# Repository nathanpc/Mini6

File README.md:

# Mini6

A mini 3 watts per channel amplifier.

## Schematic

It's a very simple amplifier with a op-amp based pre-amp and buffered volume control followed by a small power amplifier with a [CFP output stage](http://en.wikipedia.org/wiki/Sziklai_pair).

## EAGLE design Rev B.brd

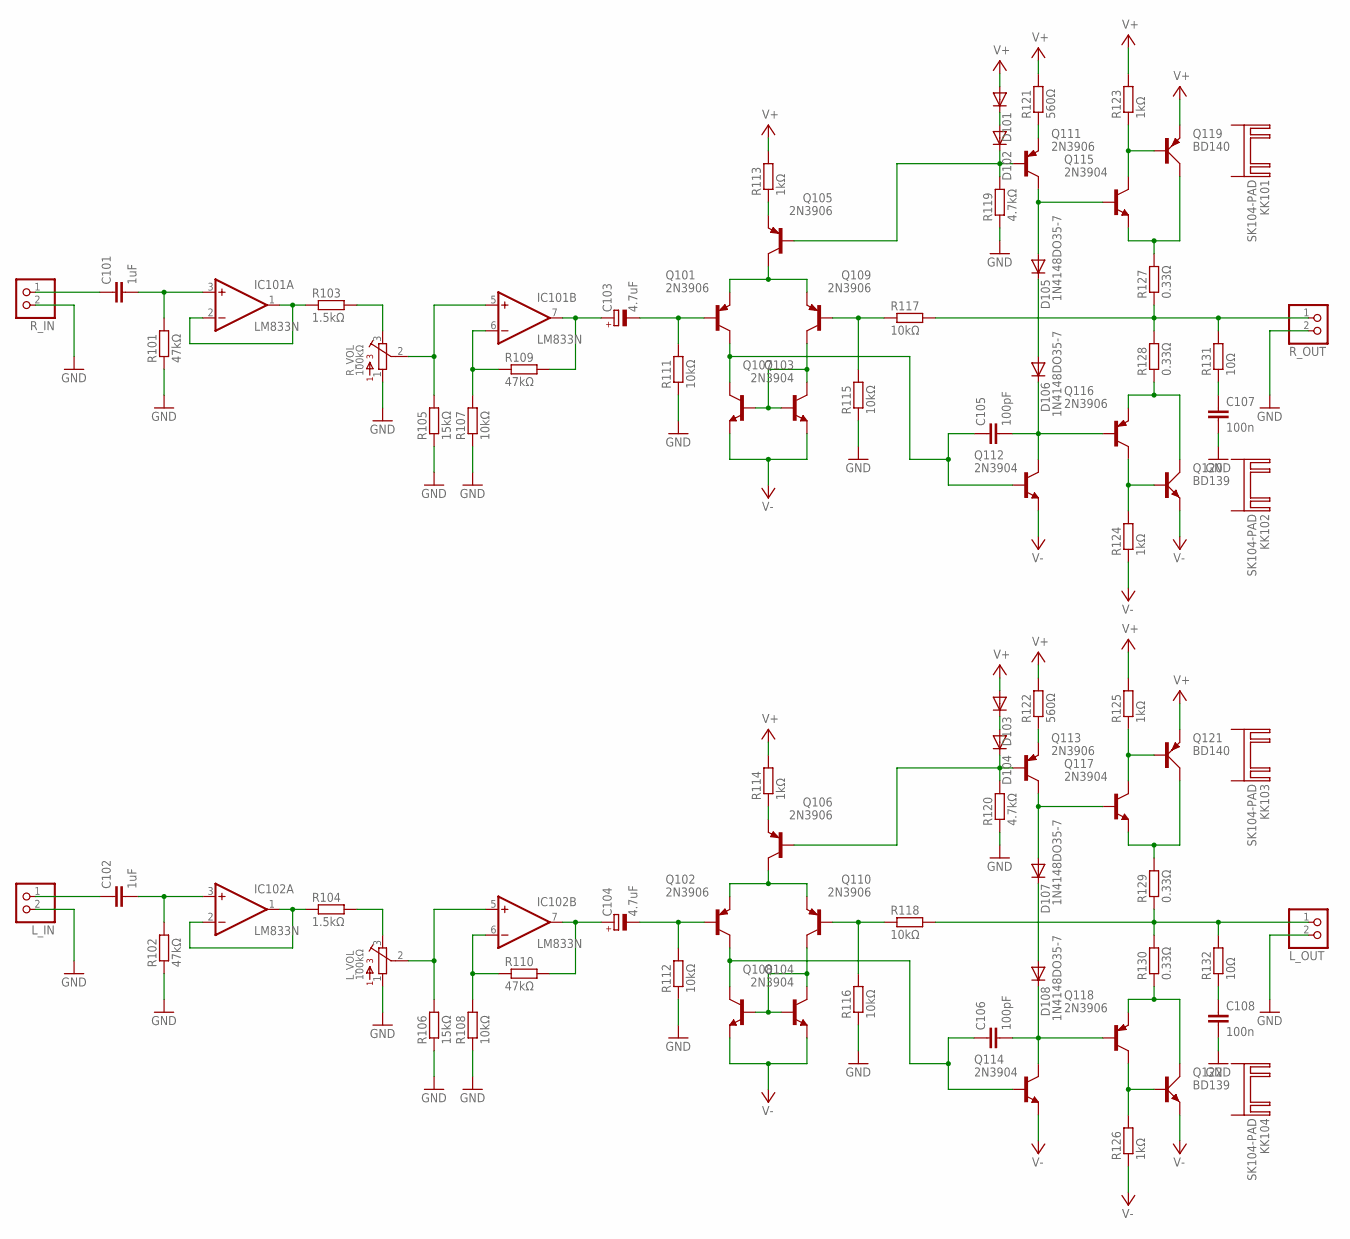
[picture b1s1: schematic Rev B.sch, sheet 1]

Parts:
C101, C102: 1uF; C150-072X183
C103, C104: 4.7uF; E2-5
C105, C106: 100pF; C050-050X075
C107, C108: 100n; C075-042X103
D101, D102, D103, D104, D105, D106, D107, D108: 1N4148DO35-7; DO35-7
IC101, IC102: LM833N; DIL08
KK101, KK102, KK103, KK104: SK104-PAD
L_IN: JST_2PIN-THM; JST-PH-2-THM
L_OUT: JST_2PIN-THM; JST-PH-2-THM
L_VOL: 100kΩ; 3362U
Q101, Q102, Q105, Q106, Q109, Q110, Q111, Q113, Q116, Q118: 2N3906; TO92
Q103, Q104, Q107, Q108, Q112, Q114, Q115, Q117: 2N3904; TO92
Q119, Q121: BD140; TO126AV
Q120, Q122: BD139; TO126AV
R101, R102, R109, R110: 47kΩ; 0207/10
R103, R104: 1.5kΩ; 0207/10
R105, R106: 15kΩ; 0207/10
R107, R108, R111, R112, R115, R116, R117, R118: 10kΩ; 0207/10
R113, R114, R123, R124, R125, R126: 1kΩ; 0207/10
R119, R120: 4.7kΩ; 0207/10
R121, R122: 560Ω; 0207/10
R127, R128, R129, R130: 0.33Ω; 0309/12
R131, R132: 10Ω; 0617V
R_IN: JST_2PIN-THM; JST-PH-2-THM
R_OUT: JST_2PIN-THM; JST-PH-2-THM
R_VOL: 100kΩ; 3362U

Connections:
GND: C107.2, C108.2, L_IN.2 (1), L_OUT.2 (1), L_VOL.1, R101.1, R102.1, R105.1, R106.1, R107.1, R108.1, R111.1, R112.1, R115.1, R116.1, R119.1, R120.1, R_IN.2 (1), R_OUT.2 (1), R_VOL.1; also elsewhere on the board
L_OUT: L_OUT.1 (2), R118.2, R129.1, R130.2, R132.2
unnamed: D105.A, Q111.1 (C), Q115.2 (B)
unnamed: Q101.3 (E), Q105.1 (C), Q109.3 (E)
unnamed: Q103.2 (B), Q107.1 (C), Q107.2 (B), Q109.1 (C)
unnamed: Q104.2 (B), Q108.1 (C), Q108.2 (B), Q110.1 (C)
unnamed: C103.-, Q101.2 (B), R111.2
unnamed: C103.+, IC101.7 (OUT), R109.2
unnamed: C101.1, R_IN.1 (2)
unnamed: C105.1, Q101.1 (C), Q103.1 (C), Q112.2 (B)
unnamed: C101.2, IC101.3 (+IN), R101.2
unnamed: IC102.1 (OUT), IC102.2 (-IN), R104.1
unnamed: IC102.5 (+IN), L_VOL.2, R106.2
unnamed: L_VOL.3, R104.2
unnamed: IC102.6 (-IN), R108.2, R110.1
unnamed: C102.1, L_IN.1 (2)
unnamed: C102.2, IC102.3 (+IN), R102.2
unnamed: Q105.3 (E), R113.1
unnamed: Q111.3 (E), R121.1
unnamed: D102.C, Q105.2 (B), Q111.2 (B), R119.2
unnamed: D101.C, D102.A
unnamed: C107.1, R131.1
unnamed: C108.1, R132.1
unnamed: Q106.3 (E), R114.1
unnamed: D105.C, D106.A
unnamed: C104.-, Q102.2 (B), R112.2
unnamed: Q115.1 (C), Q119.B, R123.1
unnamed: Q116.1 (C), Q120.B, R124.2
unnamed: Q116.3 (E), Q120.C, R128.1
unnamed: Q115.3 (E), Q119.C, R127.2
unnamed: C104.+, IC102.7 (OUT), R110.2
unnamed: C105.2, D106.C, Q112.1 (C), Q116.2 (B)
unnamed: Q109.2 (B), R115.2, R117.1
unnamed: Q102.3 (E), Q106.1 (C), Q110.3 (E)
unnamed: C106.1, Q102.1 (C), Q104.1 (C), Q114.2 (B)
unnamed: D107.C, D108.A
unnamed: D107.A, Q113.1 (C), Q117.2 (B)
unnamed: Q117.1 (C), Q121.B, R125.1
unnamed: Q117.3 (E), Q121.C, R129.2
unnamed: Q118.1 (C), Q122.B, R126.2
unnamed: Q118.3 (E), Q122.C, R130.1
unnamed: C106.2, D108.C, Q114.1 (C), Q118.2 (B)
unnamed: Q110.2 (B), R116.2, R118.1
unnamed: Q113.3 (E), R122.1
unnamed: D104.C, Q106.2 (B), Q113.2 (B), R120.2
unnamed: D103.C, D104.A
unnamed: IC101.1 (OUT), IC101.2 (-IN), R103.1
unnamed: IC101.5 (+IN), R105.2, R_VOL.2
unnamed: R103.2, R_VOL.3
unnamed: IC101.6 (-IN), R107.2, R109.1
R_OUT: R117.2, R127.1, R128.2, R131.2, R_OUT.1 (2)
V+: D101.A, D103.A, Q119.E, Q121.E, R113.2, R114.2, R121.2, R122.2, R123.2, R125.2; also elsewhere on the board
V-: Q103.3 (E), Q104.3 (E), Q107.3 (E), Q108.3 (E), Q112.3 (E), Q114.3 (E), Q120.E, Q122.E, R124.1, R126.1; also elsewhere on the board

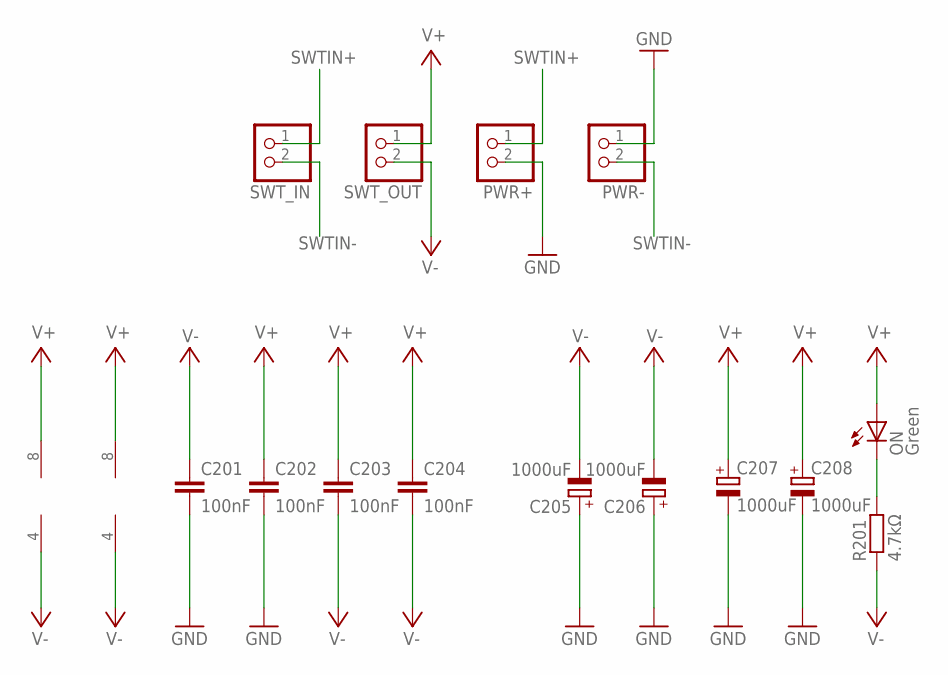
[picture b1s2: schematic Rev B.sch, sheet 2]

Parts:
C201, C202, C203, C204: 100nF; C025-025X050
C205, C206, C207, C208: 1000uF; E5-10,5
IC101, IC102: LM833N; DIL08
ON: Green; LED5MM
PWR+: JST_2PIN-THM; JST-PH-2-THM
PWR-: JST_2PIN-THM; JST-PH-2-THM
R201: 4.7kΩ; 0207/10
SWT_IN: JST_2PIN-THM; JST-PH-2-THM
SWT_OUT: JST_2PIN-THM; JST-PH-2-THM

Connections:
GND: C201.2, C202.2, C205.+, C206.+, C207.-, C208.-, PWR+.2 (1), PWR-.1 (2); also elsewhere on the board
unnamed: ON.K (C), R201.2
SWTIN+: PWR+.1 (2), SWT_IN.1 (2)
SWTIN-: PWR-.2 (1), SWT_IN.2 (1)
V+: C202.1, C203.1, C204.1, C207.+, C208.+, IC101.8 (V+), IC102.8 (V+), ON.A, SWT_OUT.1 (2); also elsewhere on the board
V-: C201.1, C203.2, C204.2, C205.-, C206.-, IC101.4 (V-), IC102.4 (V-), R201.1, SWT_OUT.2 (1); also elsewhere on the board

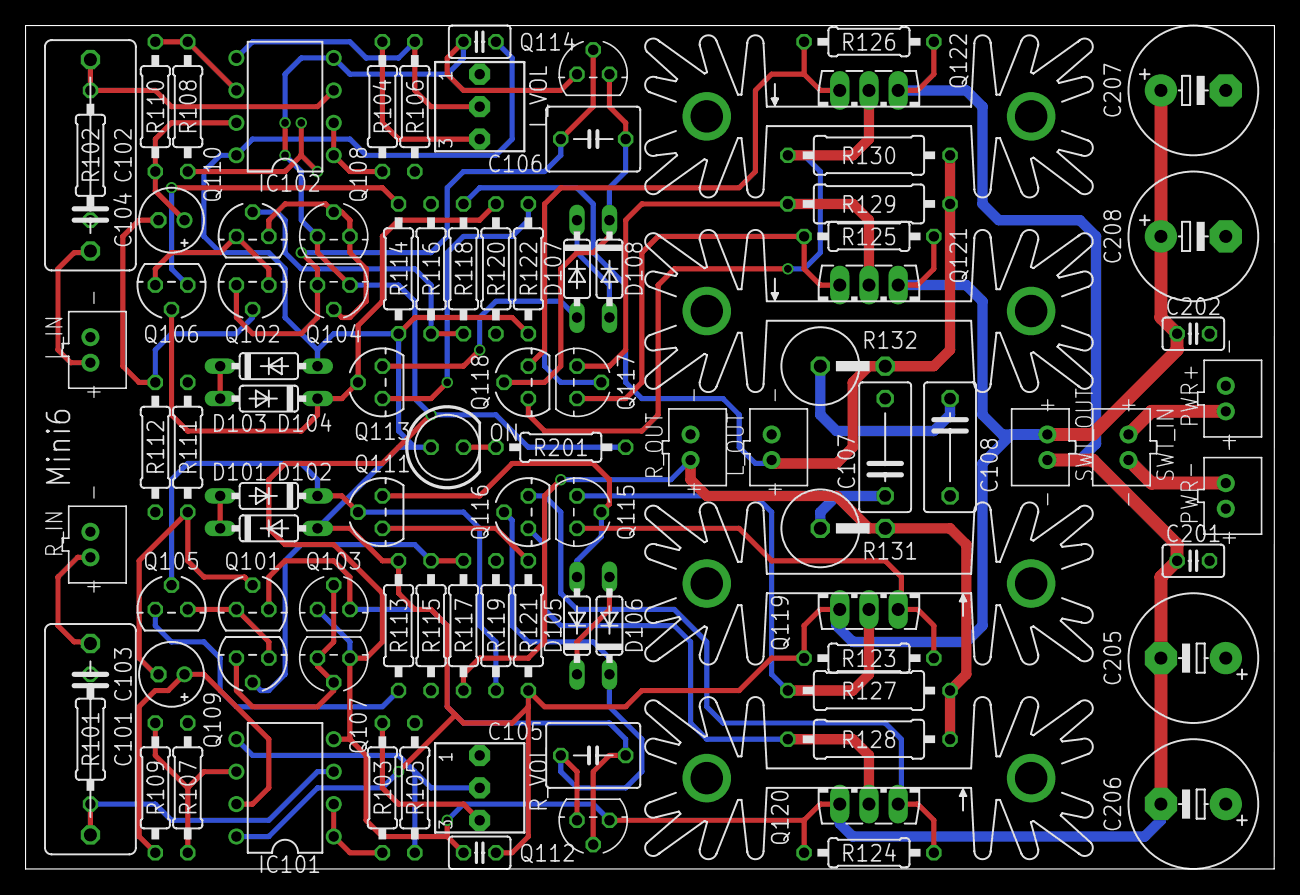
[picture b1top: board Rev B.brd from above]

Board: 4 copper layers, 97.8 x 66.0 mm, 96 parts (0 on the bottom side), 56 nets.

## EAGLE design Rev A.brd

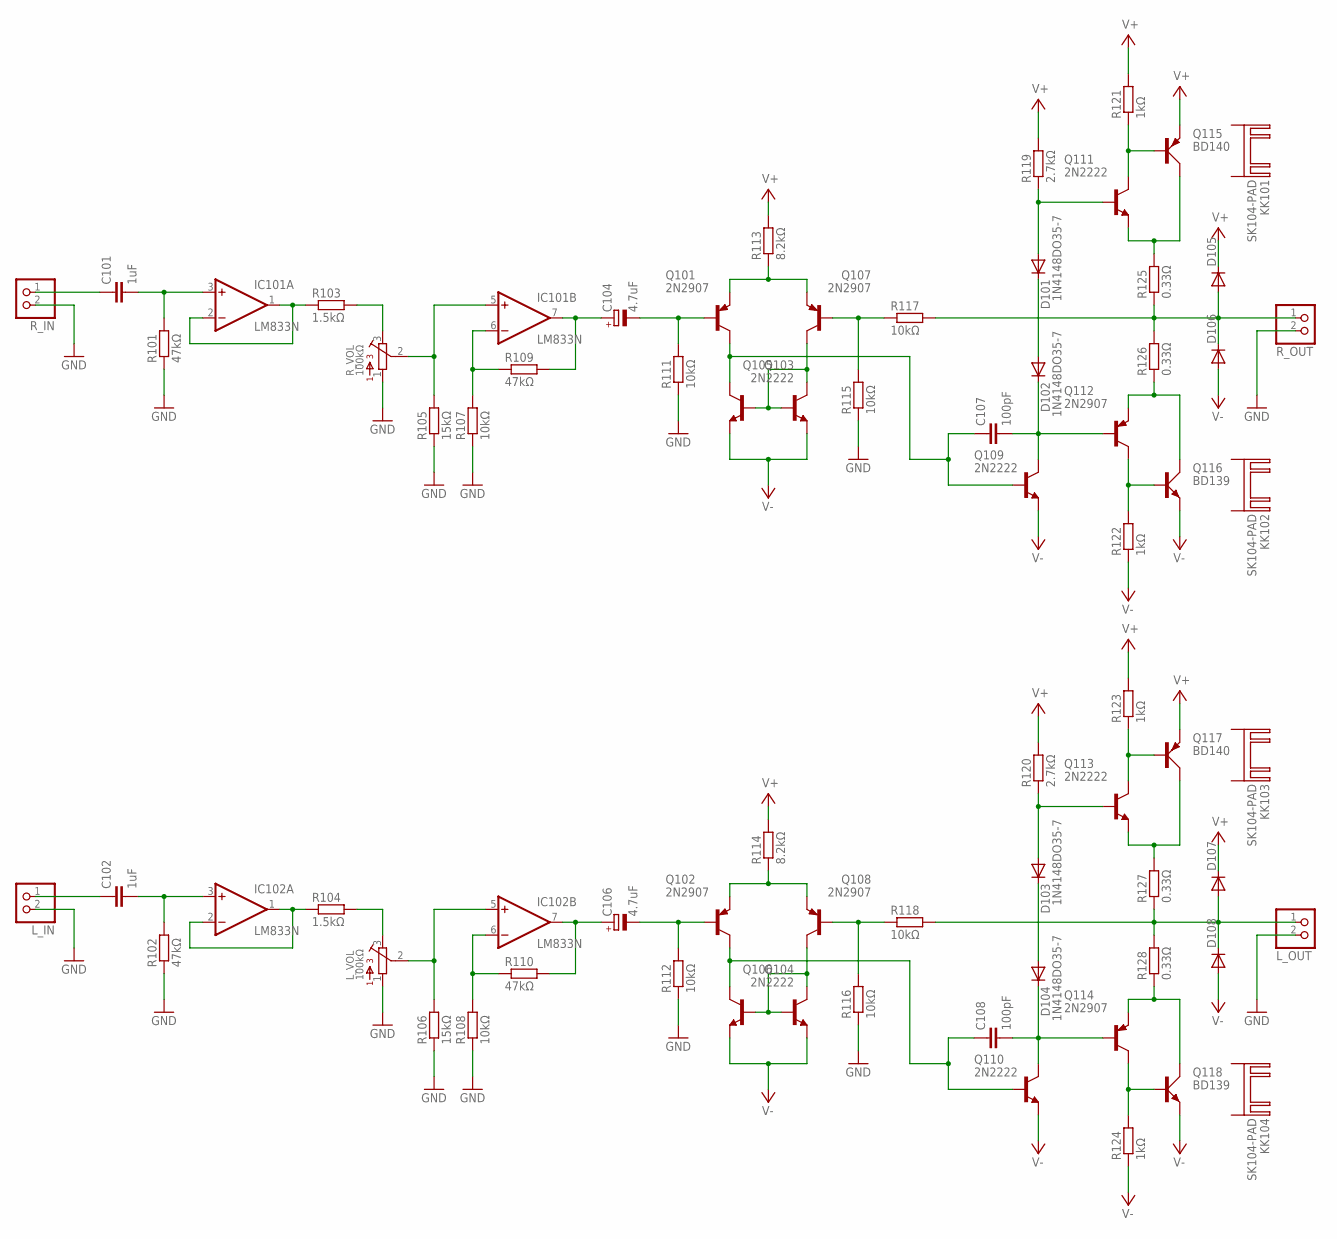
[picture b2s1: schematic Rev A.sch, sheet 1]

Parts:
C101, C102: 1uF; C050-050X075
C104, C106: 4.7uF; E2-5
C107, C108: 100pF; C050-050X075
D101, D102, D103, D104, D105, D106, D107, D108: 1N4148DO35-7; DO35-7
IC101, IC102: LM833N; DIL08
KK101, KK102, KK103, KK104: SK104-PAD
L_IN: JST_2PIN-THM; JST-PH-2-THM
L_OUT: JST_2PIN-THM; JST-PH-2-THM
L_VOL: 100kΩ; 3362U
Q101, Q102, Q107, Q108, Q112, Q114: 2N2907; TO18
Q103, Q104, Q105, Q106, Q109, Q110, Q111, Q113: 2N2222; TO18
Q115, Q117: BD140; TO126AV
Q116, Q118: BD139; TO126AV
R101, R102, R109, R110: 47kΩ; 0207/10
R103, R104: 1.5kΩ; 0207/10
R105, R106: 15kΩ; 0207/10
R107, R108, R111, R112, R115, R116, R117, R118: 10kΩ; 0207/10
R113, R114: 8.2kΩ; 0207/10
R119, R120: 2.7kΩ; 0207/10
R121, R122, R123, R124: 1kΩ; 0207/10
R125, R126, R127, R128: 0.33Ω; 0309/12
R_IN: JST_2PIN-THM; JST-PH-2-THM
R_OUT: JST_2PIN-THM; JST-PH-2-THM
R_VOL: 100kΩ; 3362U

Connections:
GND: L_IN.2 (1), L_OUT.2 (1), L_VOL.1, R101.1, R102.1, R105.1, R106.1, R107.1, R108.1, R111.1, R112.1, R115.1, R116.1, R_IN.2 (1), R_OUT.2 (1), R_VOL.1; also elsewhere on the board
L_OUT: D107.A, D108.C, L_OUT.1 (2), R118.2, R127.1, R128.2
unnamed: D101.A, Q111.2 (B), R119.1
unnamed: Q101.1 (E), Q107.1 (E), R113.1
unnamed: Q103.2 (B), Q105.2 (B), Q105.3 (C), Q107.3 (C)
unnamed: Q104.2 (B), Q106.2 (B), Q106.3 (C), Q108.3 (C)
unnamed: C104.-, Q101.2 (B), R111.2
unnamed: C104.+, IC101.7 (OUT), R109.2
unnamed: C101.1, R_IN.1 (2)
unnamed: C107.1, Q101.3 (C), Q103.3 (C), Q109.2 (B)
unnamed: C101.2, IC101.3 (+IN), R101.2
unnamed: IC102.1 (OUT), IC102.2 (-IN), R104.1
unnamed: IC102.5 (+IN), L_VOL.2, R106.2
unnamed: L_VOL.3, R104.2
unnamed: IC102.6 (-IN), R108.2, R110.1
unnamed: C102.1, L_IN.1 (2)
unnamed: C102.2, IC102.3 (+IN), R102.2
unnamed: D101.C, D102.A
unnamed: C106.-, Q102.2 (B), R112.2
unnamed: Q111.3 (C), Q115.B, R121.1
unnamed: Q112.3 (C), Q116.B, R122.2
unnamed: Q112.1 (E), Q116.C, R126.1
unnamed: Q111.1 (E), Q115.C, R125.2
unnamed: C106.+, IC102.7 (OUT), R110.2
unnamed: C107.2, D102.C, Q109.3 (C), Q112.2 (B)
unnamed: Q107.2 (B), R115.2, R117.1
unnamed: Q102.1 (E), Q108.1 (E), R114.1
unnamed: C108.1, Q102.3 (C), Q104.3 (C), Q110.2 (B)
unnamed: D103.C, D104.A
unnamed: D103.A, Q113.2 (B), R120.1
unnamed: Q113.3 (C), Q117.B, R123.1
unnamed: Q113.1 (E), Q117.C, R127.2
unnamed: Q114.3 (C), Q118.B, R124.2
unnamed: Q114.1 (E), Q118.C, R128.1
unnamed: C108.2, D104.C, Q110.3 (C), Q114.2 (B)
unnamed: Q108.2 (B), R116.2, R118.1
unnamed: IC101.1 (OUT), IC101.2 (-IN), R103.1
unnamed: IC101.5 (+IN), R105.2, R_VOL.2
unnamed: R103.2, R_VOL.3
unnamed: IC101.6 (-IN), R107.2, R109.1
R_OUT: D105.A, D106.C, R117.2, R125.1, R126.2, R_OUT.1 (2)
V+: D105.C, D107.C, Q115.E, Q117.E, R113.2, R114.2, R119.2, R120.2, R121.2, R123.2; also elsewhere on the board
V-: D106.A, D108.A, Q103.1 (E), Q104.1 (E), Q105.1 (E), Q106.1 (E), Q109.1 (E), Q110.1 (E), Q116.E, Q118.E, R122.1, R124.1; also elsewhere on the board

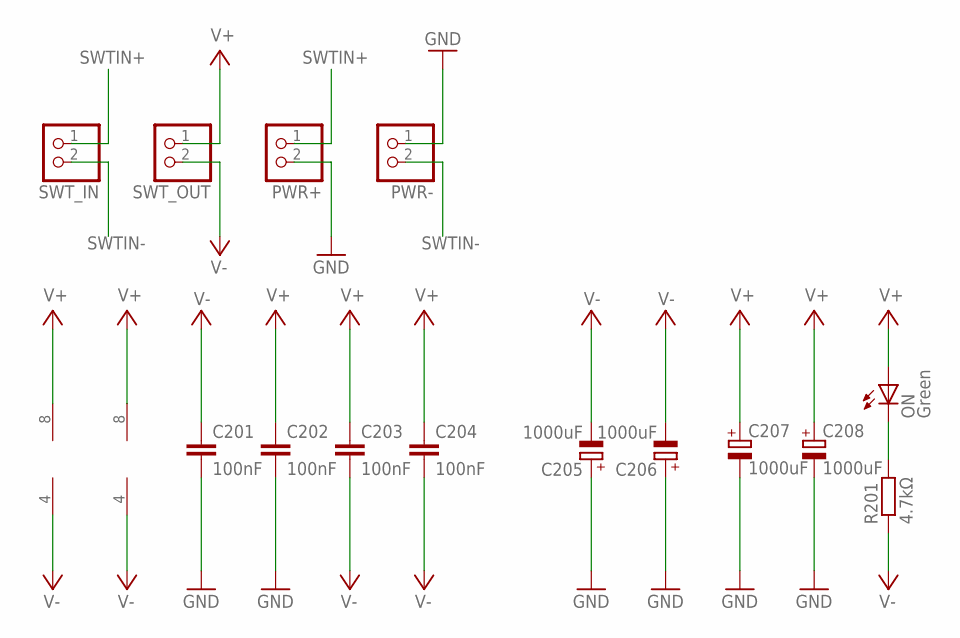
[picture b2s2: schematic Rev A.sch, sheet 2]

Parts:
C201, C202, C203, C204: 100nF; C025-025X050
C205, C206, C207, C208: 1000uF; E5-10,5
IC101, IC102: LM833N; DIL08
ON: Green; LED5MM
PWR+: JST_2PIN-THM; JST-PH-2-THM
PWR-: JST_2PIN-THM; JST-PH-2-THM
R201: 4.7kΩ; 0207/10
SWT_IN: JST_2PIN-THM; JST-PH-2-THM
SWT_OUT: JST_2PIN-THM; JST-PH-2-THM

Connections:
GND: C201.2, C202.2, C205.+, C206.+, C207.-, C208.-, PWR+.2 (1), PWR-.1 (2); also elsewhere on the board
unnamed: ON.K (C), R201.2
SWTIN+: PWR+.1 (2), SWT_IN.1 (2)
SWTIN-: PWR-.2 (1), SWT_IN.2 (1)
V+: C202.1, C203.1, C204.1, C207.+, C208.+, IC101.8 (V+), IC102.8 (V+), ON.A, SWT_OUT.1 (2); also elsewhere on the board
V-: C201.1, C203.2, C204.2, C205.-, C206.-, IC101.4 (V-), IC102.4 (V-), R201.1, SWT_OUT.2 (1); also elsewhere on the board

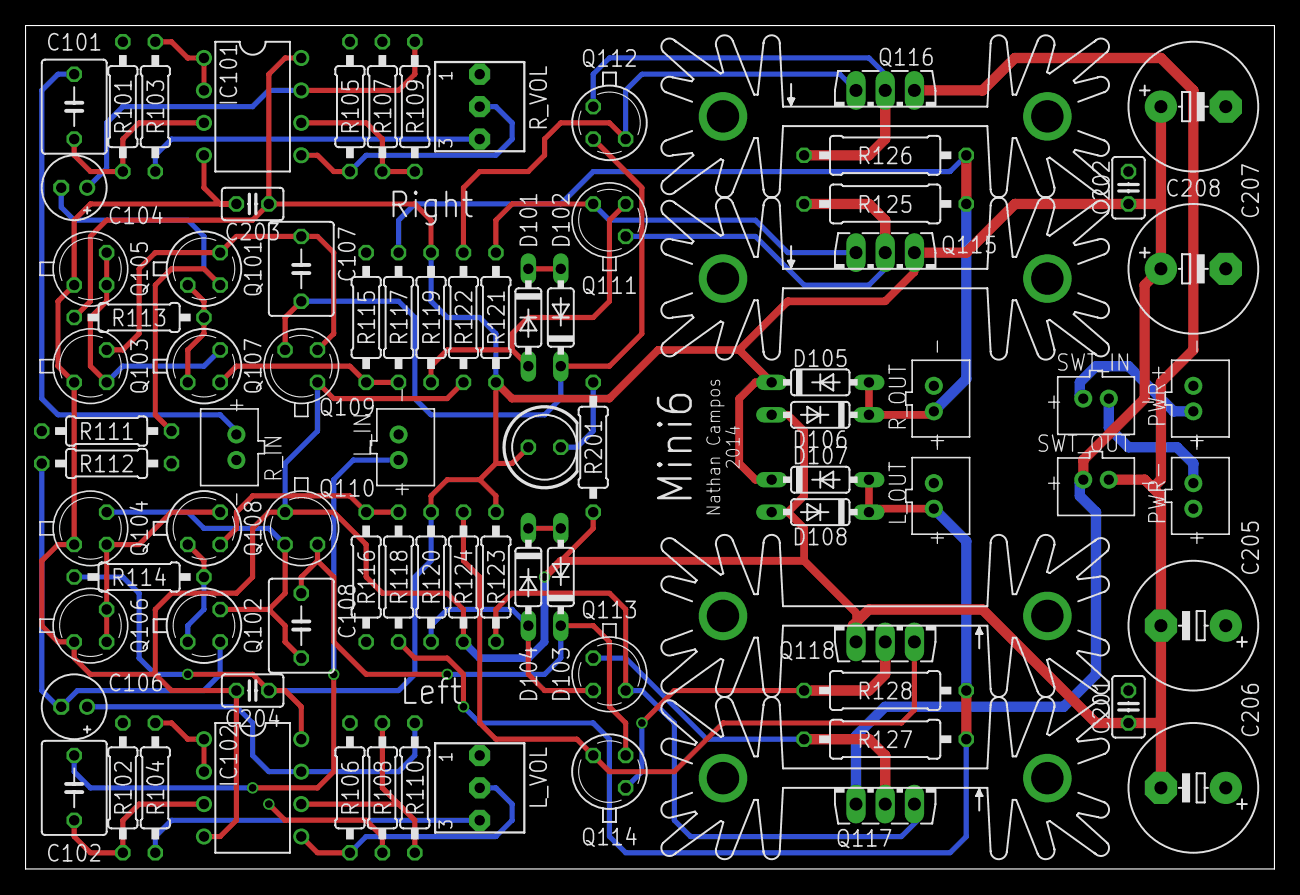
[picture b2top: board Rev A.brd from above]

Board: 4 copper layers, 97.8 x 66.0 mm, 86 parts (0 on the bottom side), 46 nets.

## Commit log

2014-08-24 First draft of the schematic
2014-08-24 Replaced all the low-power transistors with TO-18 versions
2014-08-25 Ready for production
2014-08-25 Exported the schematic and board layout
2014-10-02 Rev B
